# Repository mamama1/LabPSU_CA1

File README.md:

# LabPSU_CA1
"CheapAss 1" Atmega 1284p controlled LabPSU with basic functionality like CV and CC mode

Welcome to my "CheapAss 1" Lab PSU project, which is based on a TIP3055 power transistor and an Atmega 1284p microcontroller.<br /><br />

Specs:<br />
0 - 24V output voltage in 100 mV steps (CV mode)<br />
0 - 1A output current in 1 mA steps (CC mode)<br />
Around 1% accuracy<br />
Dual 12 Bit DAC (MCP4922)<br />
Precision 4.096V voltage reference for the DAC and Atmega-integrated ADC (MCP1541)<br />
High-side current measurement using the MAX4080F IC<br />
LM324 Quad opamp and LM358 Dual opamp<br />
Low Ripple, Low Noise<br />
One Board solution (transformer onboard)<br />
Front panel for display, buttons, LED and piezo buzzer mounting

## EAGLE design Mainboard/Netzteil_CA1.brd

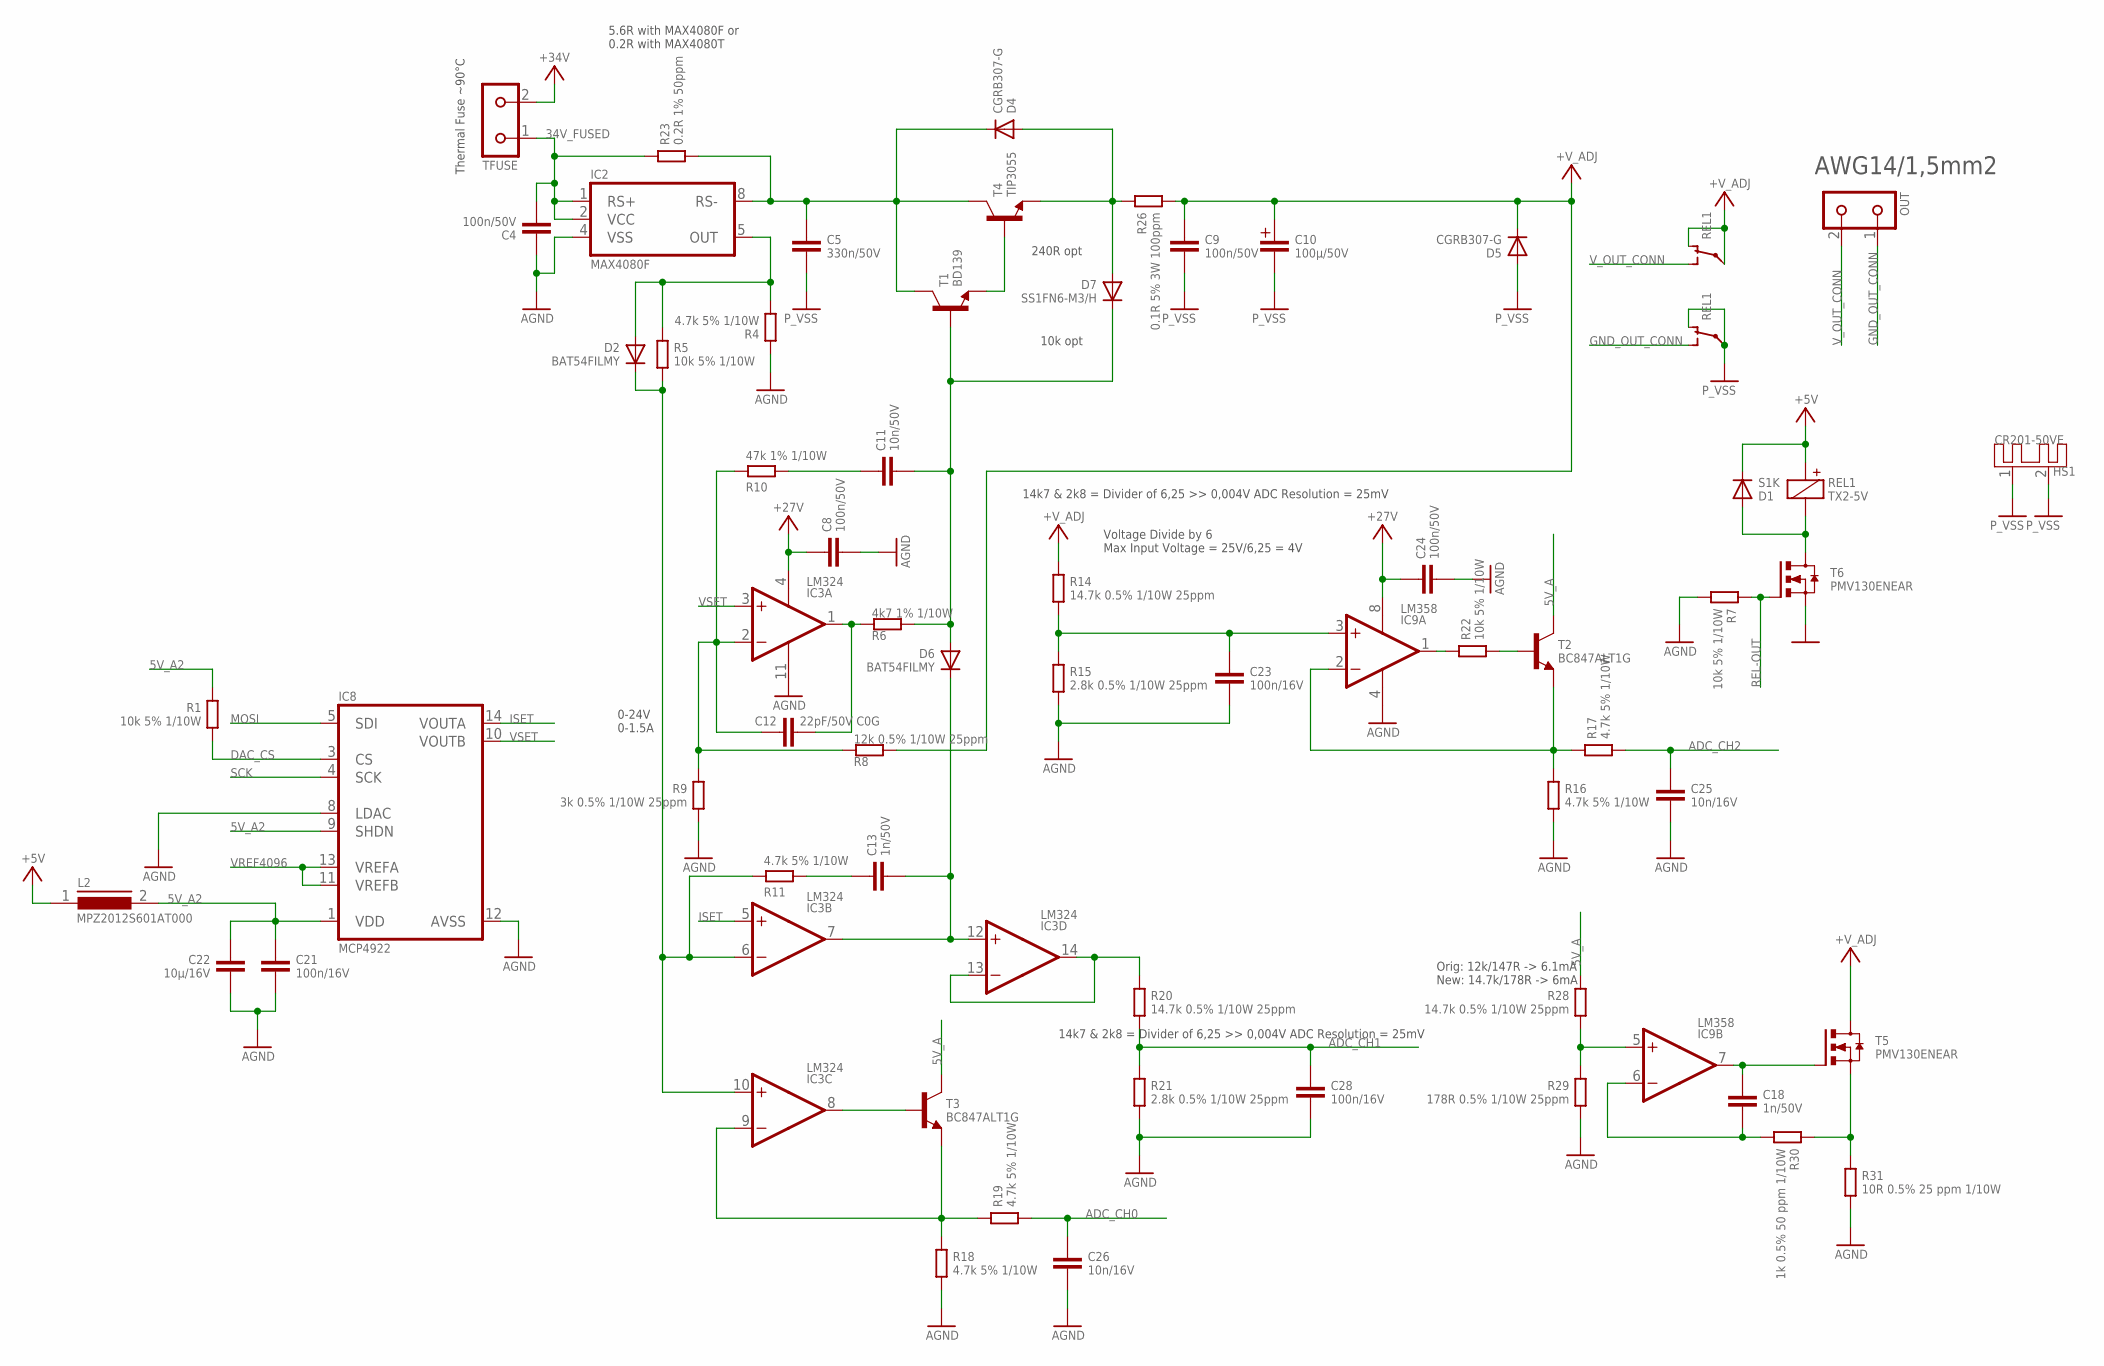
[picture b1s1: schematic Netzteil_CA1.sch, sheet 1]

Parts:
C4, C8, C9, C24: 100n/50V; 0805
C5: 330n/50V; 0805
C10: 100µ/50V; C+/3.5/8
C11: 10n/50V; 0805
C12: 22pF/50V C0G; 0805
C13, C18: 1n/50V; 0805
C21, C23, C28: 100n/16V; 0805
C22: 10µ/16V; 1206
C25, C26: 10n/16V; 0805
D1: S1K; DO214AC
D2, D6: BAT54FILMY; SOT23
D4, D5: CGRB307-G; DO214AA-CGRB307-G
D7: SS1FN6-M3/H; DO219AB-2
HS1: CR201-50VE; CR201-50
IC2: MAX4080F; SOP8
IC3: LM324; SO14
IC8: MCP4922; TSSOP14
IC9: LM358; SOP8
L2: MPZ2012S601AT000; C0805K
OUT: KL2691311500002; KL2-691311500002
R1, R5, R7, R22: 10k 5% 1/10W; C0805K
R4, R11, R16, R17, R18, R19: 4.7k 5% 1/10W; C0805K
R6: 4k7 1% 1/10W; C0805K
R8: 12k 0.5% 1/10W 25ppm; C0805K
R9: 3k 0.5% 1/10W 25ppm; C0805K
R10: 47k 1% 1/10W; C0805K
R14, R20, R28: 14.7k 0.5% 1/10W 25ppm; C0805K
R15, R21: 2.8k 0.5% 1/10W 25ppm; C0805K
R23: 0.2R 1% 50ppm; LRMAP2512
R26: 0.1R 5% 3W 100ppm; YAG_PT2512
R29: 178R 0.5% 1/10W 25ppm; C0805K
R30: 1k 0.5% 50 ppm 1/10W; C0805K
R31: 10R 0.5% 25 ppm 1/10W; C0805K
REL1: TX2-5V; REL-TX2
T1: BD139; TO126
T2, T3: BC847ALT1G; SOT23-BEC
T4: TIP3055; TOP3AV
T5, T6: PMV130ENEAR; SOT23
TFUSE: KL2691311500002; KL2-691311500002

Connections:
5V_A: R28.1, T2.C, T3.C; also elsewhere on the board
5V_A2: C21.1, C22.1, IC8.1 (VDD), IC8.9 (SHDN), L2.2, R1.1
34V_FUSED: C4.2, IC2.1 (RS+), IC2.2 (VCC), R23.1, TFUSE.1
+5V: D1.C, L2.1, REL1.+; also elsewhere on the board
+27V: C8.1, C24.1, IC3.4 (V+), IC9.8 (V+); also elsewhere on the board
+34V: TFUSE.2; also elsewhere on the board
+V_ADJ: C9.1, C10.+, D5.C, R8.1, R14.1, R26.2, REL1.O1 (O), REL1.P1, T5.3 (D)
ADC_CH0: C26.1, R19.2; also elsewhere on the board
ADC_CH1: C28.1, R20.2, R21.1; also elsewhere on the board
ADC_CH2: C25.1, R17.2; also elsewhere on the board
AGND: C4.1, C8.2, C21.2, C22.2, C23.2, C24.2, C25.2, C26.2, C28.2, IC2.4 (VSS), IC3.11 (V-), IC8.8 (LDAC), IC8.12 (AVSS), IC9.4 (V-), R4.1, R7.2, R9.2, R15.2, R16.2, R18.2, R21.2, R29.2, R31.2; also elsewhere on the board
DAC_CS: IC8.3 (CS), R1.2; also elsewhere on the board
GND_OUT_CONN: OUT.1, REL1.S2 (S)
ISET: IC3.5 (+IN), IC8.14 (VOUTA)
MOSI: IC8.5 (SDI); also elsewhere on the board
unnamed: C5.1, D4.C, IC2.8 (RS-), R23.2, T1.2 (C), T4.C
unnamed: D2.1 (A), IC2.5 (OUT), R4.2, R5.1
unnamed: D2.3 (C), IC3.6 (-IN), IC3.10 (+IN), R5.2, R11.2
unnamed: C12.2, IC3.1 (OUT), R6.2
unnamed: C11.2, D6.1 (A), D7.C, R6.1, T1.3 (B)
unnamed: C11.1, R10.1
unnamed: C13.2, D6.3 (C), IC3.7 (OUT), IC3.12 (+IN)
unnamed: IC3.13 (-IN), IC3.14 (OUT), R20.1
unnamed: C13.1, R11.1
unnamed: D1.A, REL1.-, T6.3 (D)
unnamed: IC9.1 (OUT), R22.1
unnamed: C23.1, IC9.3 (+IN), R14.2, R15.1
unnamed: C12.1, IC3.2 (-IN), R8.2, R9.1, R10.2
unnamed: IC9.2 (-IN), R16.1, R17.1, T2.E
unnamed: IC3.9 (-IN), R18.1, R19.1, T3.E
unnamed: R22.2, T2.B
unnamed: IC9.5 (+IN), R28.2, R29.1
unnamed: D4.A, D7.A, R26.1, T4.E
unnamed: IC3.8 (OUT), T3.B
unnamed: C18.2, IC9.6 (-IN), R30.2
unnamed: C18.1, IC9.7 (OUT), T5.1 (G)
unnamed: T1.1 (E), T4.B
unnamed: R30.1, R31.1, T5.2 (S)
P_VSS: C5.2, C9.2, C10.-, D5.A, HS1.1, HS1.2, REL1.O2 (O), REL1.P2; also elsewhere on the board
REL-OUT: R7.1, T6.1 (G); also elsewhere on the board
SCK: IC8.4 (SCK); also elsewhere on the board
VREF4096: IC8.11 (VREFB), IC8.13 (VREFA); also elsewhere on the board
VSET: IC3.3 (+IN), IC8.10 (VOUTB)
VSS: T6.2 (S); also elsewhere on the board
V_OUT_CONN: OUT.2, REL1.S1 (S)

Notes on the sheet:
Voltage Divide by 6 Max Input Voltage = 25V/6,25 = 4V
0-24V 0-1.5A
240R opt
10k opt
14k7 & 2k8 = Divider of 6,25 >> 0,004V ADC Resolution = 25mV
Orig: 12k/147R -> 6.1mA New: 14.7k/178R -> 6mA
5.6R with MAX4080F or 0.2R with MAX4080T
AWG14/1,5mm2
Thermal Fuse ~90°C

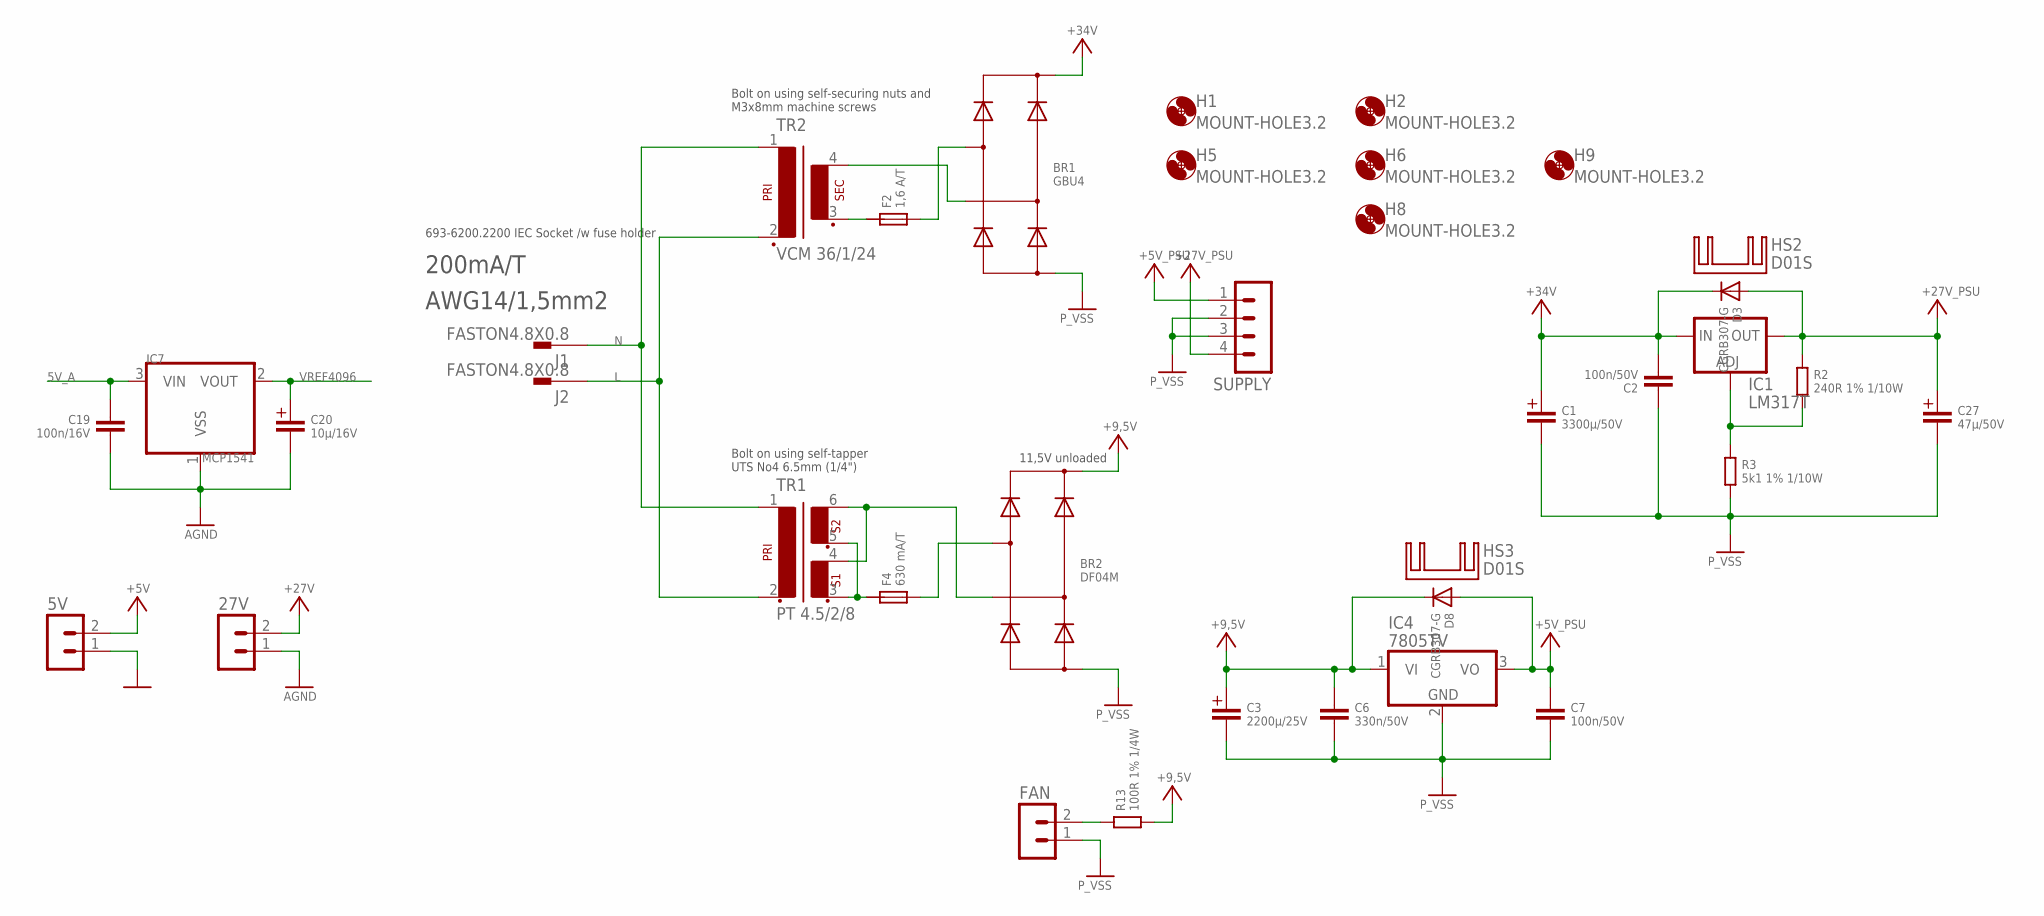
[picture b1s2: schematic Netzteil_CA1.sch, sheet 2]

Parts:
5V, 27V: JST-PH-2.0-2P
BR1: GBU4; GBU4S
BR2: DF04M; BR-DIL2
C1: 3300µ/50V; C+/7.5/18
C2, C7: 100n/50V; 0805
C3: 2200µ/25V; C+/5/12.5
C6: 330n/50V; 0805
C19: 100n/16V; 0805
C20: 10µ/16V; C+/1.5/4
C27: 47µ/50V; C+/2.5/6.3
D3, D8: CGRB307-G; DO214AA-CGRB307-G
F2: 1,6 A/T; F5X20
F4: 630 mA/T; F5X20
FAN: JST-PH-2.0-2P
H1, H2, H5, H6, H8, H9: MOUNT-HOLE3.2; 3,2
HS2, HS3: D01S
IC1: LM317T; 317TS
IC4: 7805TV; TO220V
IC7: MCP1541; TO92-G
J1, J2: FASTON4.8X0.8; FASTON-4.8X0.8
R2: 240R 1% 1/10W; C0805K
R3: 5k1 1% 1/10W; C0805K
R13: 100R 1% 1/4W; C0805K
SUPPLY: JST-PH-2.0-4P
TR1: PT 4.5/2/8; PT/4,5/2/..
TR2: VCM 36/1/24; VCM36/1/24

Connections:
5V_A: C19.1, IC7.3 (VIN); also elsewhere on the board
+5V: 5V.2; also elsewhere on the board
+5V_PSU: C7.1, D8.A, IC4.3 (VO), SUPPLY.1
+9,5V: BR2.DC+, C3.+, C6.1, D8.C, IC4.1 (VI), R13.2
+27V: 27V.2; also elsewhere on the board
+27V_PSU: C27.+, D3.A, IC1.2 (OUT), R2.1, SUPPLY.4
+34V: BR1.+ (DC+), C1.+, C2.2, D3.C, IC1.3 (IN); also elsewhere on the board
AGND: 27V.1, C19.2, C20.-, IC7.1 (VSS); also elsewhere on the board
L: J2.A1, J2.A2, TR1.2, TR2.2
N: J1.A1, J1.A2, TR1.1, TR2.1
unnamed: IC1.1 (ADJ), R2.2, R3.1
unnamed: BR2.AC1, F4.3 (2), F4.4 (2)
unnamed: F2.1, F2.2 (1), TR2.3 (S3)
unnamed: BR1.AC1, F2.3 (2), F2.4 (2)
unnamed: BR1.AC2, TR2.4 (S4)
unnamed: F4.1, F4.2 (1), TR1.3, TR1.5
unnamed: BR2.AC2, TR1.4, TR1.6
unnamed: FAN.2, R13.1
P_VSS: BR1.- (DC-), BR2.DC-, C1.-, C2.1, C3.-, C6.2, C7.2, C27.-, FAN.1, IC4.2 (GND), R3.2, SUPPLY.2, SUPPLY.3; also elsewhere on the board
VREF4096: C20.+, IC7.2 (VOUT); also elsewhere on the board
VSS: 5V.1; also elsewhere on the board

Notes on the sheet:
11,5V unloaded
AWG14/1,5mm2
200mA/T
693-6200.2200 IEC Socket /w fuse holder
Bolt on using self-securing nuts and M3x8mm machine screws
Bolt on using self-tapper UTS No4 6.5mm (1/4")

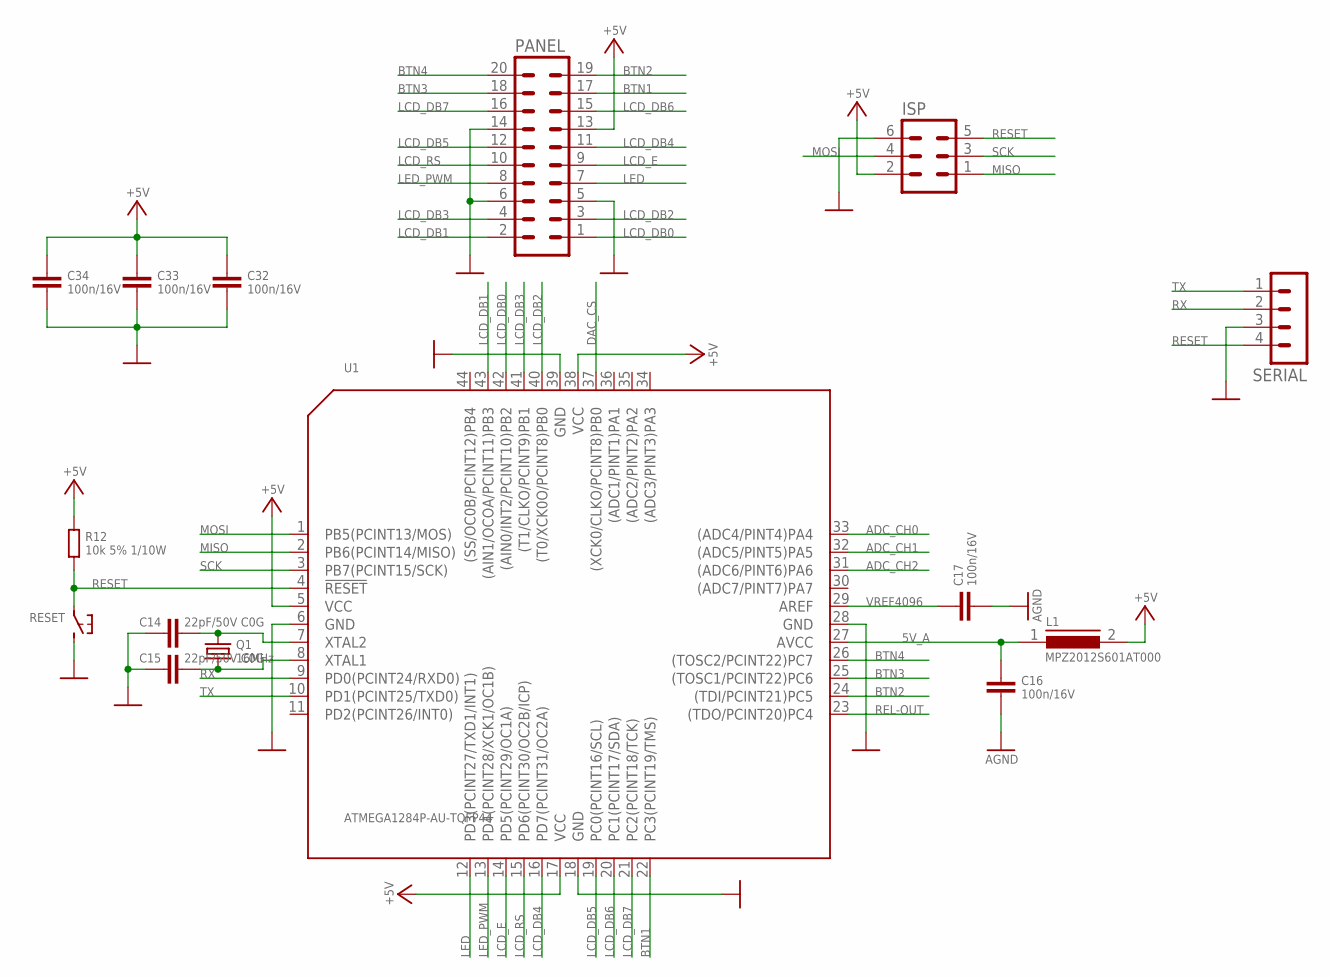
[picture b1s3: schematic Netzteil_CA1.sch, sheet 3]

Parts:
C14, C15: 22pF/50V C0G; 0805
C16, C17, C32, C33, C34: 100n/16V; 0805
ISP: ML6
L1: MPZ2012S601AT000; C0805K
PANEL: MA10-2
Q1: 16MHz; Q-5X3.2MM-TXC-7A.SERIES
R12: 10k 5% 1/10W; C0805K
RESET: TS1B3F-10XX; B3F-10XX
SERIAL: MA04-1
U1: ATMEGA1284P-AU-TQFP44; TQFP44-0.8-9.6X9.6MM

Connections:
5V_A: C16.1, L1.1, U1.27 (AVCC); also elsewhere on the board
+5V: C32.1, C33.1, C34.1, ISP.2, L1.2, PANEL.13, R12.1, U1.5 (VCC), U1.17 (VCC), U1.38 (VCC); also elsewhere on the board
ADC_CH0: U1.33 ((ADC4/PINT4)PA4); also elsewhere on the board
ADC_CH1: U1.32 ((ADC5/PINT5)PA5); also elsewhere on the board
ADC_CH2: U1.31 ((ADC6/PINT6)PA6); also elsewhere on the board
AGND: C16.2, C17.2; also elsewhere on the board
BTN1: PANEL.17, U1.22 (PC3(PCINT19/TMS))
BTN2: PANEL.19, U1.24 ((TDI/PCINT21)PC5)
BTN3: PANEL.18, U1.25 ((TOSC1/PCINT22)PC6)
BTN4: PANEL.20, U1.26 ((TOSC2/PCINT22)PC7)
DAC_CS: U1.37 ((XCK0/CLKO/PCINT8)PB0); also elsewhere on the board
LCD_DB0: PANEL.1, U1.42 ((AIN0/INT2/PCINT10)PB2)
LCD_DB1: PANEL.2, U1.43 ((AIN1/OCOA/PCINT11)PB3)
LCD_DB2: PANEL.3, U1.40 ((T0/XCK0O/PCINT8)PB0)
LCD_DB3: PANEL.4, U1.41 ((T1/CLKO/PCINT9)PB1)
LCD_DB4: PANEL.11, U1.16 (PD7(PCINT31/OC2A))
LCD_DB5: PANEL.12, U1.19 (PC0(PCINT16/SCL))
LCD_DB6: PANEL.15, U1.20 (PC1(PCINT17/SDA))
LCD_DB7: PANEL.16, U1.21 (PC2(PCINT18/TCK))
LCD_E: PANEL.9, U1.14 (PD5(PCINT29/OC1A))
LCD_RS: PANEL.10, U1.15 (PD6(PCINT30/OC2B/ICP))
LED: PANEL.7, U1.12 (PD3(PCINT27/TXD1/INT1))
LED_PWM: PANEL.8, U1.13 (PD4(PCINT28/XCK1/OC1B))
MISO: ISP.1, U1.2 (PB6(PCINT14/MISO))
MOSI: ISP.4, U1.1 (PB5(PCINT13/MOS)); also elsewhere on the board
unnamed: C14.2, Q1.2, U1.7 (XTAL2)
unnamed: C15.2, Q1.1, U1.8 (XTAL1)
REL-OUT: U1.23 ((TDO/PCINT20)PC4); also elsewhere on the board
RESET: ISP.5, R12.2, RESET.1, SERIAL.4, U1.4 (!RESET)
RX: SERIAL.2, U1.9 (PD0(PCINT24/RXD0))
SCK: ISP.3, U1.3 (PB7(PCINT15/SCK)); also elsewhere on the board
TX: SERIAL.1, U1.10 (PD1(PCINT25/TXD0))
VREF4096: C17.1, U1.29 (AREF); also elsewhere on the board
VSS: C14.1, C15.1, C32.2, C33.2, C34.2, ISP.6, PANEL.5, PANEL.6, PANEL.14, RESET.3 (2), SERIAL.3, U1.6 (GND), U1.18 (GND), U1.28 (GND), U1.39 (GND); also elsewhere on the board

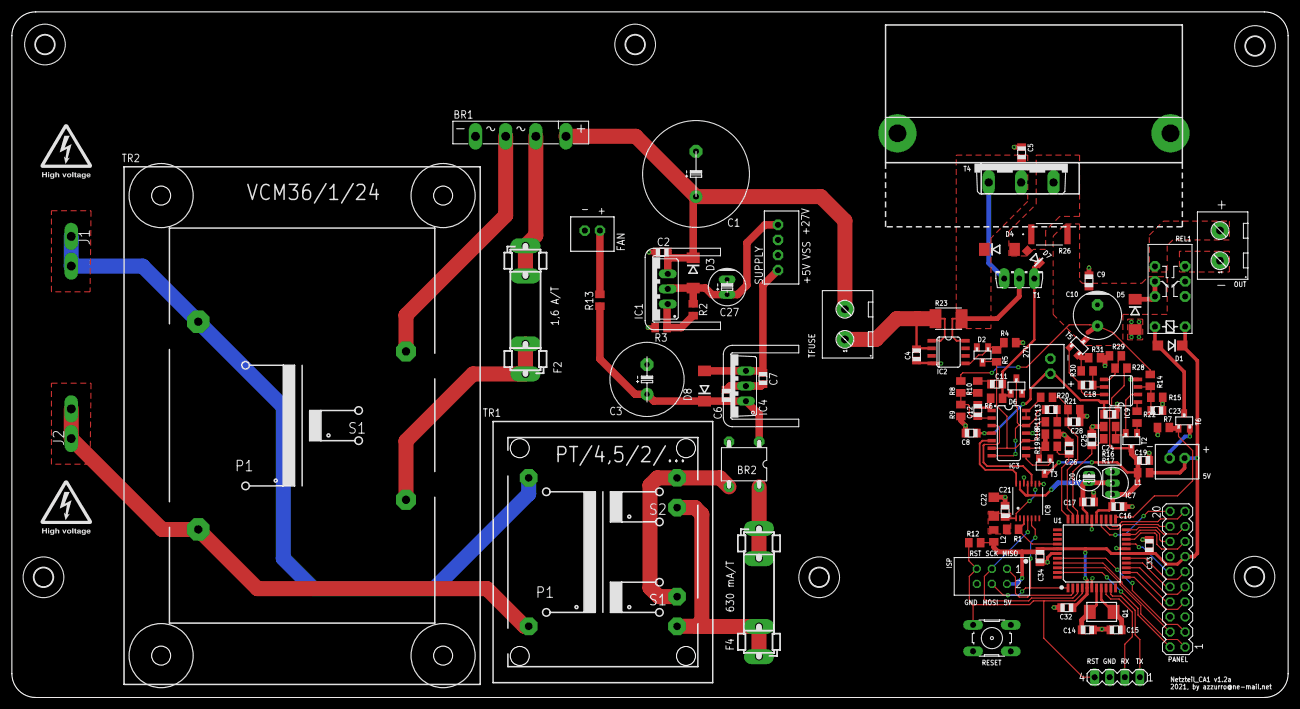
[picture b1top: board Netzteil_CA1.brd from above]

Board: 2 copper layers, 215.0 x 115.5 mm, 115 parts (0 on the bottom side), 80 nets.

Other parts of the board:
U$10: CASE-Z17
U$18: IEC-C14-FUSED-6200.2200
U$21: FAN60X25

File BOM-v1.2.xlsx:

Qty | Value | Parts | OC_CONRAD | OC_CONRAD_ADD | OC_DIGIKEY | OC_MOUSER | OC_MOUSER_ADD | OC_MOUSER_ALT | OC_MOUSER_ALT2_OLD | OC_MOUSER_ALT_OLD | OC_MOUSER_OLD | OC_RS | OC_RS_ADD | OC_RS_ADD2 | REMARKS
1 |  | FAN |  |  | 455-1704-ND |  | 369-MF60251V21UA99 |  |  |  |  |  |  |  | JST-PH Buchse und Lüfter
2 |  | 5V, 27V |  |  | 455-1704-ND
1 |  | SUPPLY |  |  | 455-1706-ND
1 |  | OUT |  |  |  | 710-691311500002 | 565-6883 |  |  |  |  |  |  |  | Printklemme und Schraubklemme für Frontpanel
1 |  | TFUSE |  |  |  | 710-691311500002 |  |  |  |  |  |  | 712-7284 |  | Printklemme und Thermosicherung
1 |  | SERIAL |  |  |  | 200-TSW10407TS
1 |  | PANEL |  |  |  | 200-TSW10707FD |  |  |  |  |  | 289-9896 | 832-3516 |  | Stiftleiste, IDC Stecker und IDC Flachbandkabel
1 |  | ISP |  |  |  | 200-TSW10307TD
1 |  | RESET |  |  |  | 653-B3F-1022
1 | 0.1R 5% 3W 100ppm | R26 |  |  |  | 652-CRA2512FZR100ELF
1 | 0.2R 1% 50ppm | R23 |  |  |  | 756-LRMAP2512R20FT4
1 | 1 A/T | F4 |  |  |  | 693-0751.0110
1 | 1,6 A/T | F2 |  |  |  | 693-0751.0110
1 | 100R 1% 1/4W | R13 |  |  |  | 660-RK73H2ATTD75R0F
9 | 100n/16V | C16, C17, C19, C21, C23, C28, C32, C33, C34 |  |  |  | 810-C2012X7R2A104K
6 | 100n/50V | C2, C4, C7, C8, C9, C24 |  |  |  | 810-C2012X7R2A104K
1 | 100µ/50V | C10 |  |  |  | 667-EEU-FR1H101
1 | 10R 0.5% 25 ppm 1/10W | R31 |  |  |  | 660-RN732ATTD10R0D25 |  | 279-2-1625868-7
5 | 10k 5% 1/10W | R1, R5, R7, R12, R22 |  |  |  | 652-CR0805-JW-103ELF
2 | 10n/16V | C25, C26 |  |  |  | 80-C0805C103K1R
1 | 10n/50V | C11 |  |  |  | 80-C0805C103K1R
1 | 10µ/16V | C20 |  |  |  | 647-USV1C100MFD1TP
1 | 10µ/16V | C22 |  |  |  | 963-TMK316AB7106KL-T
1 | 12k 0.5% 1/10W 25ppm | R8 |  |  |  | 754-RR1220P-123D
3 | 14.7k 0.5% 1/10W 25ppm | R14, R20, R28 |  |  |  | 754-RR1220P-1472D-M |  |  |  |  | 754-RR1220P-123D | 708-6470
1 | 16MHz | Q1 |  |  |  | 717-7A-16.000MAAJ-T
1 | 178R 0.5% 1/10W 25ppm | R29 |  |  |  | 754-RR1220P-1780D-M |  |  | 667-ERA-6AEB1470V | 754-RR1220P-151D | 754-RR1220P-1470D-M | 708-9340
1 | 1k 0.5% 50 ppm 1/10W | R30 |  |  |  | 754-RR1220P-102D
2 | 1n/50V | C13, C18 |  |  |  | 603-CC805KRX7R0BB102
2 | 2.8k 0.5% 1/10W 25ppm | R15, R21 |  |  |  | 754-RR1220P-2801D-M |  |  |  |  | 754-RR1220P-242D | 708-6250
1 | 2200µ/25V | C3 |  |  |  | 667-EEU-FS1E222
3 | 22pF/50V C0G | C12, C14, C15 |  |  |  | 603-CC805JRNPO9BN220
1 | 240R 1% 1/10W | R2 |  |  |  | 652-CR0805FX-2400ELF
1 | 3300µ/50V | C1 |  |  |  | 667-EEU-HD1H332 |  | 647-UVZ1H332MHD
2 | 330n/50V | C5, C6 |  |  |  | 80-C0805C334K5RECTU
1 | 3k 0.5% 1/10W 25ppm | R9 |  |  |  | 754-RR1220P-302D
6 | 4.7k 5% 1/10W | R4, R11, R16, R17, R18, R19 |  |  |  | 652-CR0805-JW-472ELF
1 | 47k 1% 1/10W | R10 |  |  |  | 652-CR0805FX-4702ELF
1 | 47µ/50V | C27 |  |  |  | 667-EEU-FR1H470
1 | 4k7 1% 1/10W | R6 |  |  |  | 652-CR0805FX-1001ELF
1 | 5k1 1% 1/10W | R3 |  |  |  | 652-CR0805FX-5101ELF
1 | 7805TV | IC4 |  |  |  | 511-L7805CV
1 | ATMEGA1284P-AU-TQFP44 | U1 |  |  |  | 556-ATMEGA1284P-AU
2 | BAT54FILMY | D2, D6 |  |  |  | 511-BAT54FILMY
2 | BC847ALT1G | T2, T3 |  |  |  | 863-BC847ALT1G
1 | BD139 | T1 |  |  |  | 511-BD139-10
4 | CGRB307-G | D3, D4, D5, D8 |  |  |  | 750-CGRB307-G
1 | CR201-50VE | HS1 |  |  |  | 588-CR201-50VE | 567-CD-02-05-247-N |  |  |  |  |  |  |  | Kühlkörper und Silpad
2 | D01S | HS2, HS3 |  |  |  | 532-576802B00
1 | DF04M | BR2 |  |  |  | 621-DF04M |  | 512-DF04M
2 | FASTON4.8X0.8 | J1, J2 | 736079 | 1022092 |  |  |  |  |  |  |  |  |  |  | Flachsteckhülsen und Lötstifte
1 | GBU4 | BR1 |  |  |  | 833-GBU4JL-BP
1 | LM317T | IC1 |  |  |  | 511-LM317T
1 | LM324 | IC3 |  |  |  | 595-LM324ADR
1 | LM358 | IC9 |  |  |  | 595-LM358ADR
1 | MAX4080F | IC2 |  |  |  | 700-MAX4080FASA
1 | MCP1541 | IC7 |  |  |  | 579-MCP1541ITO
1 | MCP4922 | IC8 |  |  |  | 579-MCP4922T-E/ST
1 | MOUNT-HOLE3.2 | H2 |  |  |  |  |  |  |  |  |  | 184-2740 | 291-379 | 161-3689 | Nylonschraube, Nylonmutter und Kunststoff-Abstandshalter
5 | MOUNT-HOLE3.2 | H1, H5, H6, H8, H9 |  |  |  |  |  |  |  |  |  | 546-5604
2 | MPZ2012S601AT000 | L1, L2 |  |  |  | 810-MPZ2012S601AT000
2 | PMV130ENEAR | T5, T6 |  |  |  | 771-PMV130ENEAR
1 | PT 4.5/2/8 | TR1 |  |  |  |  |  |  |  |  |  | 201-8463 | 546-5604 |  | Trafo und selbstschneidende Schrauben
1 | S1K | D1 |  |  |  | 512-S1K
1 | SS1FN6-M3/H | D7 |  |  |  | 78-SS1FN6-M3/H
1 | TIP3055 | T4 |  |  |  | 863-TIP3055G
1 | TX2-5V | REL1 |  |  |  | 769-TX2-5V
1 | VCM 36/1/24 | TR2 |  |  |  |  |  |  |  |  |  | 732-0506

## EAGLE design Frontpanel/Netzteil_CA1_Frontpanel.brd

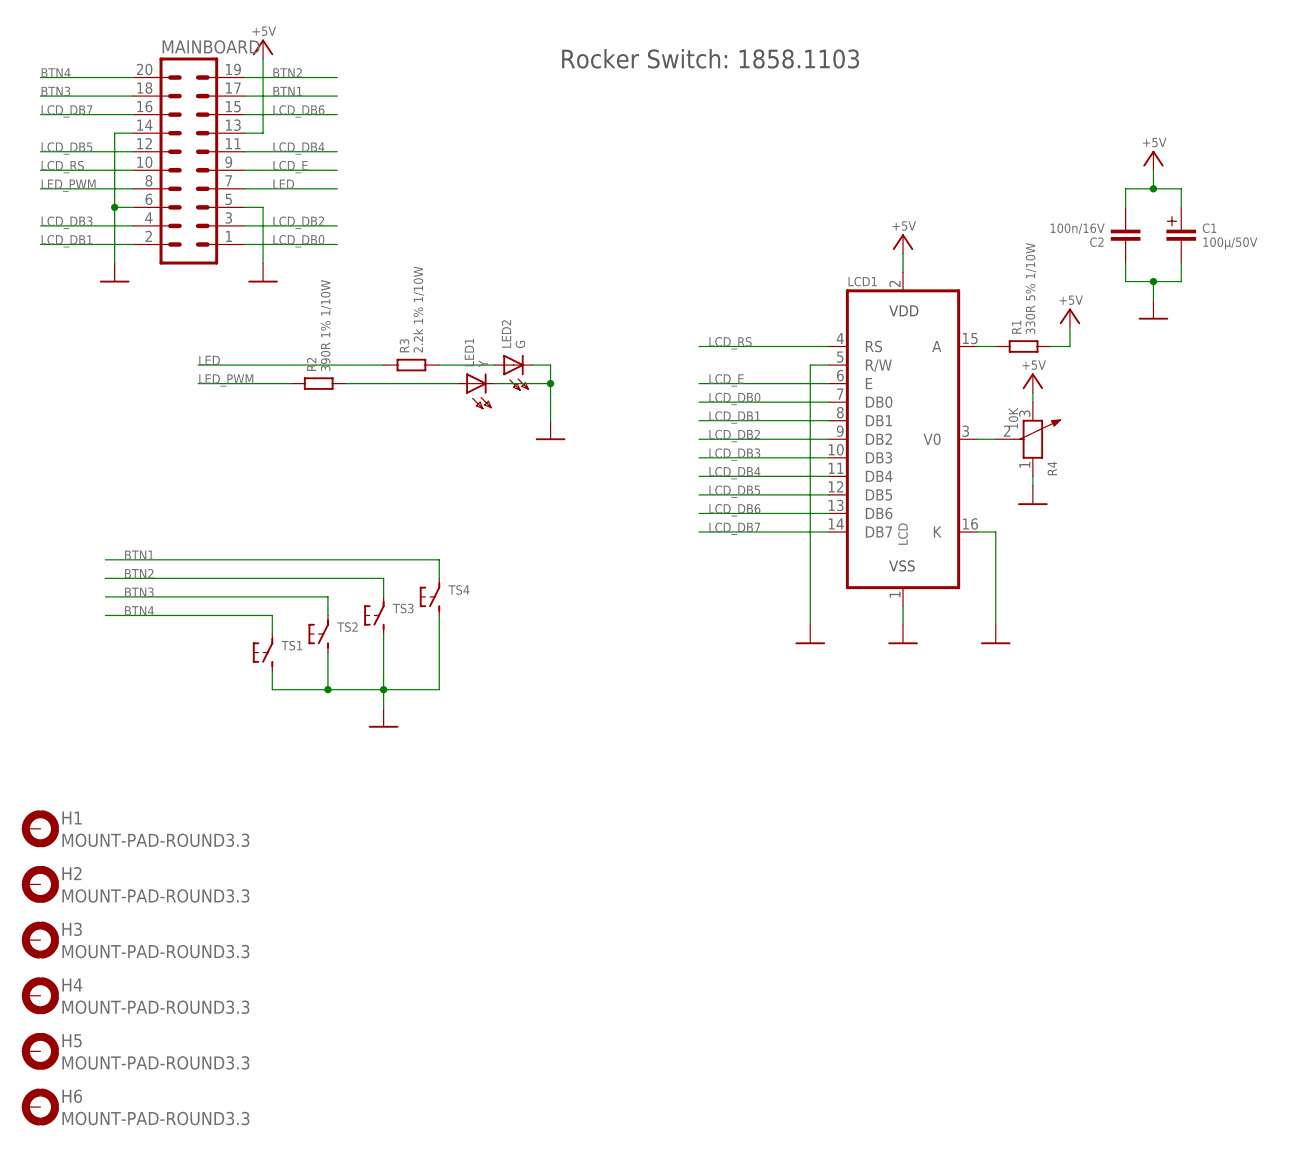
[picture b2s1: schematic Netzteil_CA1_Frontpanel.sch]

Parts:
C1: 100µ/50V; C+/3.5/8
C2: 100n/16V; 0805
H1, H2, H3, H4, H5, H6: MOUNT-PAD-ROUND3.3; 3,3-PAD
LCD1: LCD; DISPLAYTECH-204C
LED1: Y; LED0805
LED2: G; LED0805
MAINBOARD: MA10-2
R1: 330R 5% 1/10W; C0805K
R2: 390R 1% 1/10W; C0805K
R3: 2.2k 1% 1/10W; C0805K
R4: 10K; ADJR3-7.0X7.0X5.0MM
TS1, TS2, TS3, TS4: TS1B3F-10XX; B3F-10XX

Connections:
+5V: C1.+, C2.2, LCD1.2 (VDD), MAINBOARD.13, R1.2, R4.3
BTN1: MAINBOARD.17, TS4.1
BTN2: MAINBOARD.19, TS3.1
BTN3: MAINBOARD.18, TS2.1
BTN4: MAINBOARD.20, TS1.1
LCD_DB0: LCD1.7 (DB0), MAINBOARD.1
LCD_DB1: LCD1.8 (DB1), MAINBOARD.2
LCD_DB2: LCD1.9 (DB2), MAINBOARD.3
LCD_DB3: LCD1.10 (DB3), MAINBOARD.4
LCD_DB4: LCD1.11 (DB4), MAINBOARD.11
LCD_DB5: LCD1.12 (DB5), MAINBOARD.12
LCD_DB6: LCD1.13 (DB6), MAINBOARD.15
LCD_DB7: LCD1.14 (DB7), MAINBOARD.16
LCD_E: LCD1.6 (E), MAINBOARD.9
LCD_RS: LCD1.4 (RS), MAINBOARD.10
LED: MAINBOARD.7, R3.1
LED_PWM: MAINBOARD.8, R2.1
unnamed: LCD1.3 (V0), R4.2
unnamed: LCD1.15 (A), R1.1
unnamed: LED2.A, R3.2
unnamed: LED1.A, R2.2
VSS: C1.-, C2.1, LCD1.1 (VSS), LCD1.5 (R/W), LCD1.16 (K), LED1.C, LED2.C, MAINBOARD.5, MAINBOARD.6, MAINBOARD.14, R4.1, TS1.3 (2), TS2.3 (2), TS3.3 (2), TS4.3 (2)

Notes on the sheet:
Rocker Switch: 1858.1103

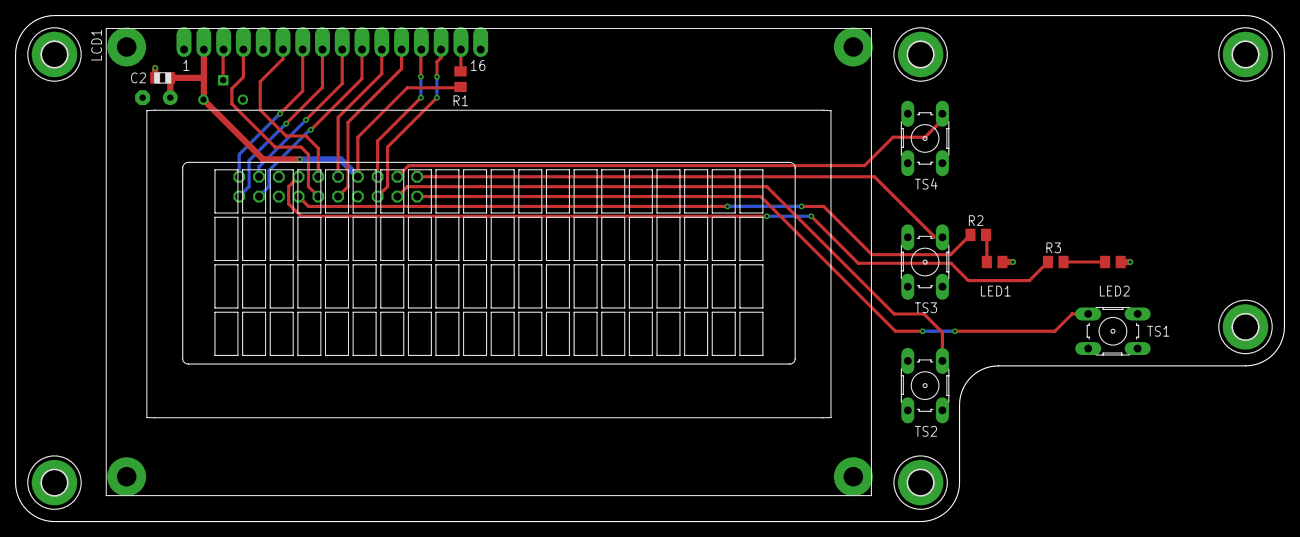
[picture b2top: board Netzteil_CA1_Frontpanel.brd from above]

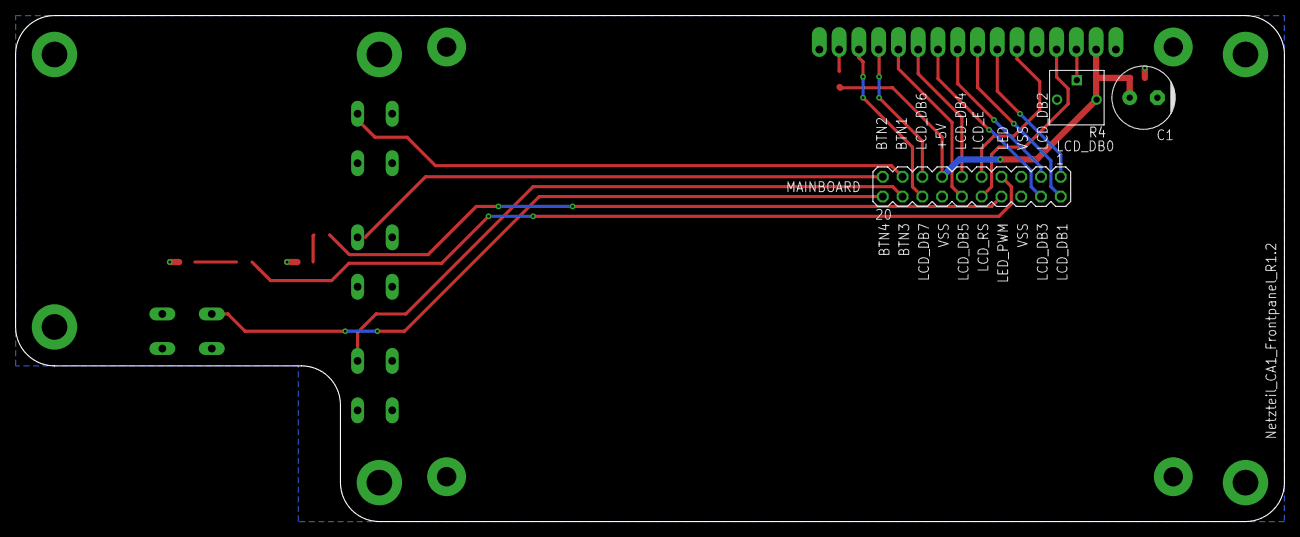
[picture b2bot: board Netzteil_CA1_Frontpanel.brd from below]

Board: 2 copper layers, 163.0 x 65.0 mm, 20 parts (3 on the bottom side), 22 nets.

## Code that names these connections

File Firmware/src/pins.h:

#ifndef pins_h
	#define pins_h

	// ##### Pin definitions

	#define DAC_CS							A0 //18
	
	#define BUTTON_DOWN_PIN					22
	#define BUTTON_UP_PIN					19
	#define BUTTON_ENTER_PIN				21
	#define BUTTON_OUTPUT_PIN				23
	#define LED_STATUS_PIN					12
	#define LED_OUTPUT_PIN					11
	#define LCD_RS_PIN						14
	#define LCD_EN_PIN						13
	#define LCD_DB0_PIN						2
	#define LCD_DB1_PIN						3
	#define LCD_DB2_PIN						0
	#define LCD_DB3_PIN						1
	#define LCD_DB4_PIN						15
	#define LCD_DB5_PIN						16
	#define LCD_DB6_PIN						17
	#define LCD_DB7_PIN						18
	#define REL_OUT_PIN						20

	#define ADC_CURRENT_READ_CH				A4 //A1	// onboard current sensing		### A1
	#define ADC_OVRCRNT_DET_CH				A5 //A2	// overcurrent detection		### A2
	#define ADC_VOLTAGE_READ_CH				A6
#endif

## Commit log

2019-07-12 initial release
2019-07-12 move a via
2019-07-12 correction of top soldermask
2021-05-18 add STLs
2021-05-18 add photos
2021-05-18 Add Firmware
